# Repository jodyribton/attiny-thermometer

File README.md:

# ATtiny84 Thermometer

A simple thermometer with an ATtiny84 driving two multiplexed seven-segment displays.

The MCU is assumed to be running at 1MHz.

# TODO
- Add schematic
- Add photos

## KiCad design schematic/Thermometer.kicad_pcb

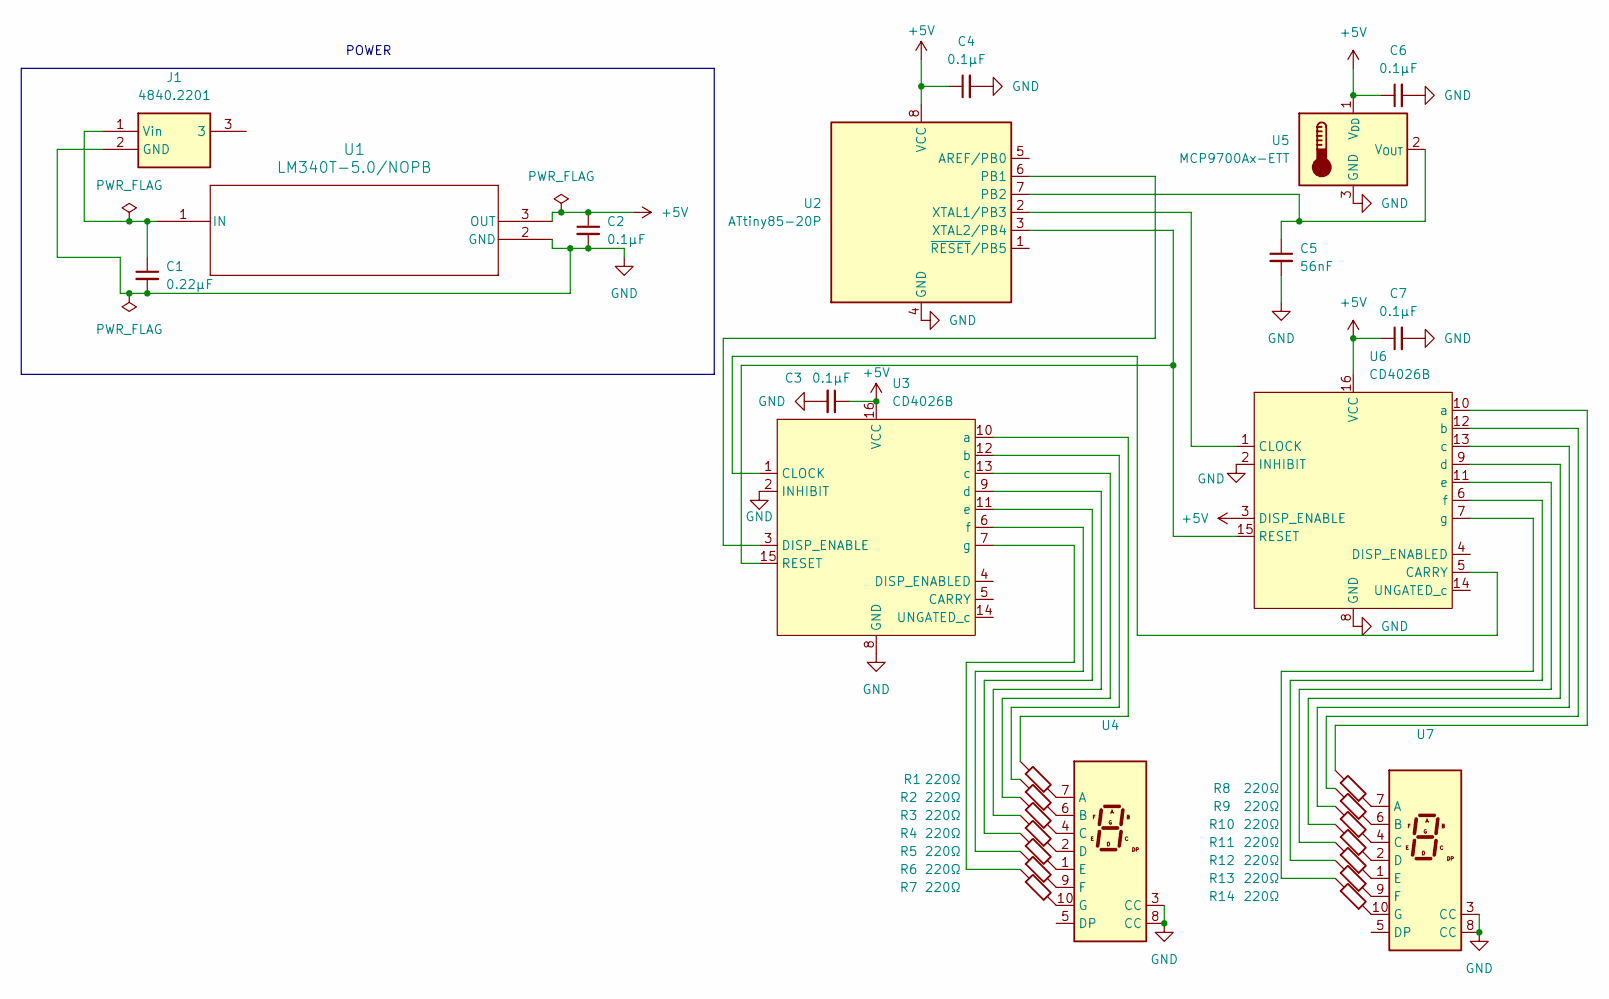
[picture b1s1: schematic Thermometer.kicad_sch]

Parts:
C1: 0.22µF; C_Disc_D8.0mm_W5.0mm_P5.00mm
C2, C3, C4, C6, C7: 0.1µF; C_Disc_D8.0mm_W5.0mm_P5.00mm
C5: 56nF; C_Disc_D8.0mm_W5.0mm_P5.00mm
J1: 4840.2201; BarrelJack_48402201; Manufacturer_Part_Number 4840.2201; Mouser Part Number 693-4840.2201
R1, R2, R3, R4, R5, R6, R7, R8, R9, R10, R11, R12, R13, R14: 220Ω; R_Axial_DIN0309_L9.0mm_D3.2mm_P12.70mm_Horizontal
U1: LM340T-5.0/NOPB; TO-220-3_Vertical
U2: ATtiny85-20P; DIP-8_W7.62mm_Socket
U3, U6: CD4026B; DIP-16_W7.62mm
U4, U7: SC56-21SURKWA
U5: MCP9700Ax-ETT; TO-92

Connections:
+5V: C2.1, C3.1, C4.1, C6.1, C7.1, U1.3 (OUT), U2.8 (VCC), U3.16 (VCC), U5.1 (V_{DD}), U6.3 (DISP_ENABLE), U6.16 (VCC)
GND: C1.2, C2.2, C3.2, C4.2, C5.2, C6.2, C7.2, J1.2 (GND), U1.2 (GND), U2.4 (GND), U3.2 (INHIBIT), U3.8 (GND), U4.3 (CC), U4.8 (CC), U5.3 (GND), U6.2 (INHIBIT), U6.8 (GND), U7.3 (CC), U7.8 (CC)
unnamed: C1.1, J1.1 (Vin), U1.1 (IN)
unnamed: U2.6 (PB1), U3.3 (DISP_ENABLE)
unnamed: C5.1, U2.7 (PB2), U5.2 (V_{OUT})
unnamed: U2.2 (XTAL1/PB3), U6.1 (CLOCK)
unnamed: U2.3 (XTAL2/PB4), U3.15 (RESET), U6.15 (RESET)
unnamed: U3.1 (CLOCK), U6.5 (CARRY)
unnamed: R1.1, U3.10 (a)
unnamed: R2.1, U3.12 (b)
unnamed: R3.1, U3.13 (c)
unnamed: R4.1, U3.9 (d)
unnamed: R5.1, U3.11 (e)
unnamed: R6.1, U3.6 (f)
unnamed: R7.1, U3.7 (g)
unnamed: R1.2, U4.7 (A)
unnamed: R2.2, U4.6 (B)
unnamed: R3.2, U4.4 (C)
unnamed: R4.2, U4.2 (D)
unnamed: R5.2, U4.1 (E)
unnamed: R6.2, U4.9 (F)
unnamed: R7.2, U4.10 (G)
unnamed: R8.1, U6.10 (a)
unnamed: R9.1, U6.12 (b)
unnamed: R10.1, U6.13 (c)
unnamed: R11.1, U6.9 (d)
unnamed: R12.1, U6.11 (e)
unnamed: R13.1, U6.6 (f)
unnamed: R14.1, U6.7 (g)
unnamed: R8.2, U7.7 (A)
unnamed: R9.2, U7.6 (B)
unnamed: R10.2, U7.4 (C)
unnamed: R11.2, U7.2 (D)
unnamed: R12.2, U7.1 (E)
unnamed: R13.2, U7.9 (F)
unnamed: R14.2, U7.10 (G)

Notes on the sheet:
POWER

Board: 2 copper layers, 29 parts (0 on the bottom side), 36 nets, no tracks yet.

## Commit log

2025-12-14 Basic schematic and first version of source.
2025-12-14 Average temperature over 10 sensor reads
2025-12-14 Don't cast accumulated temp before division
2026-01-03 Clean up schematic directory
2026-06-07 Basic, fully working multiplexed thermometer.
